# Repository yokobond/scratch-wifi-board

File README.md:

# scratch-wifi-board
Arduino and WiFi(ESP8266) speaking Scratch-Remote-Sensor-Protocol

## Overview

- [esp4scratch](esp4scratch) is a sketch for ESP8266/Arduino
- [esp4scratch_arduino](esp4scratch_arduino) is a sketch for Arduino Board which connect to ESP8266.
- [hardware/eagle](hardware/eagle) is a design data of Scratch WiFi Shield.

## Licence

[MIT](LICENCE)

## Author

[yokobond](https://github.com/yokobond)

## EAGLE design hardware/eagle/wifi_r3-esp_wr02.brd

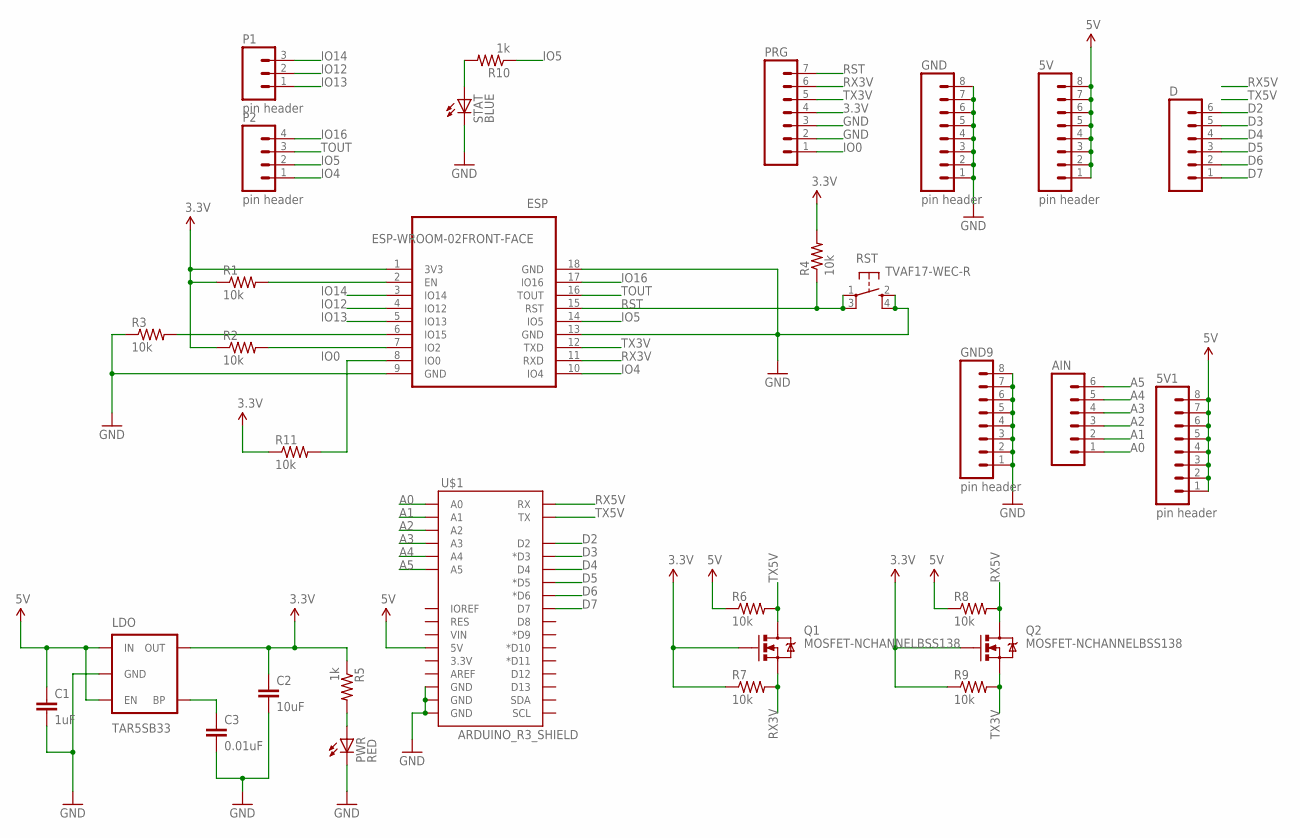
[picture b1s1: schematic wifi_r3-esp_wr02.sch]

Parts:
5V, 5V1: pin header; 1X08
AIN: M06SIP; 1X06
C1: 1uF; 0603-CAP
C2: 10uF; 0805
C3: 0.01uF; 0603-CAP
D: M06SIP; 1X06
ESP: ESP-WROOM-02FRONT-FACE; FRONT-FACE
GND, GND9: pin header; 1X08
LDO: TAR5SB33; SOT23-5
P1: pin header; 1X03
P2: pin header; 1X04
PRG: M07; 1X07
PWR: RED; LED-0603
Q1, Q2: MOSFET-NCHANNELBSS138; SOT23
R1, R2, R3, R4, R6, R7, R8, R9, R11: 10k; 0603-RES
R5, R10: 1k; 0603-RES
RST: TVAF17-WEC-R; KMR2
STAT: BLUE; LED-0603
U$1: ARDUINO_R3_SHIELD; UNO_R3_SHIELD

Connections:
3.3V: C2.1, ESP.1 (3V3), LDO.5 (OUT), PRG.4, Q1.1 (G), Q2.1 (G), R1.1, R2.1, R4.2, R5.1, R7.1, R9.1, R11.1
5V: 5V.1, 5V.2, 5V.3, 5V.4, 5V.5, 5V.6, 5V.7, 5V.8, 5V1.1, 5V1.2, 5V1.3, 5V1.4, 5V1.5, 5V1.6, 5V1.7, 5V1.8, C1.1, LDO.1 (IN), LDO.3 (EN), R6.1, R8.1, U$1.5V
A0: AIN.1, U$1.A0
A1: AIN.2, U$1.A1
A2: AIN.3, U$1.A2
A3: AIN.4, U$1.A3
A4: AIN.5, U$1.A4
A5: AIN.6, U$1.A5
D2: D.6, U$1.D2
D3: D.5, U$1.D3 (*D3)
D4: D.4, U$1.D4
D5: D.3, U$1.D5 (*D5)
D6: D.2, U$1.D6 (*D6)
D7: D.1, U$1.D7
GND: C1.2, C2.2, C3.2, ESP.9 (GND), ESP.13 (GND), ESP.18 (GND), GND.1, GND.2, GND.3, GND.4, GND.5, GND.6, GND.7, GND.8, GND9.1, GND9.2, GND9.3, GND9.4, GND9.5, GND9.6, GND9.7, GND9.8, LDO.2 (GND), PRG.2, PRG.3, PWR.C, R3.1, RST.2 (S), RST.4 (S), STAT.C, U$1.GND@0 (GND), U$1.GND@1 (GND), U$1.GND@2 (GND)
IO0: ESP.8 (IO0), PRG.1, R11.2
IO4: ESP.10 (IO4), P2.1
IO5: ESP.14 (IO5), P2.2, R10.1
IO12: ESP.4 (IO12), P1.2
IO13: ESP.5 (IO13), P1.1
IO14: ESP.3 (IO14), P1.3
IO16: ESP.17 (IO16), P2.4
unnamed: ESP.2 (EN), R1.2
unnamed: ESP.7 (IO2), R2.2
unnamed: ESP.6 (IO15), R3.2
unnamed: PWR.A, R5.2
unnamed: R10.2, STAT.A
unnamed: C3.1, LDO.4 (BP)
RST: ESP.15 (RST), PRG.7, R4.1, RST.1, RST.3
RX3V: ESP.11 (RXD), PRG.6, Q1.2 (S), R7.2
RX5V: Q2.3 (D), R8.2, U$1.RX
TOUT: ESP.16 (TOUT), P2.3
TX3V: ESP.12 (TXD), PRG.5, Q2.2 (S), R9.2
TX5V: Q1.3 (D), R6.2, U$1.TX

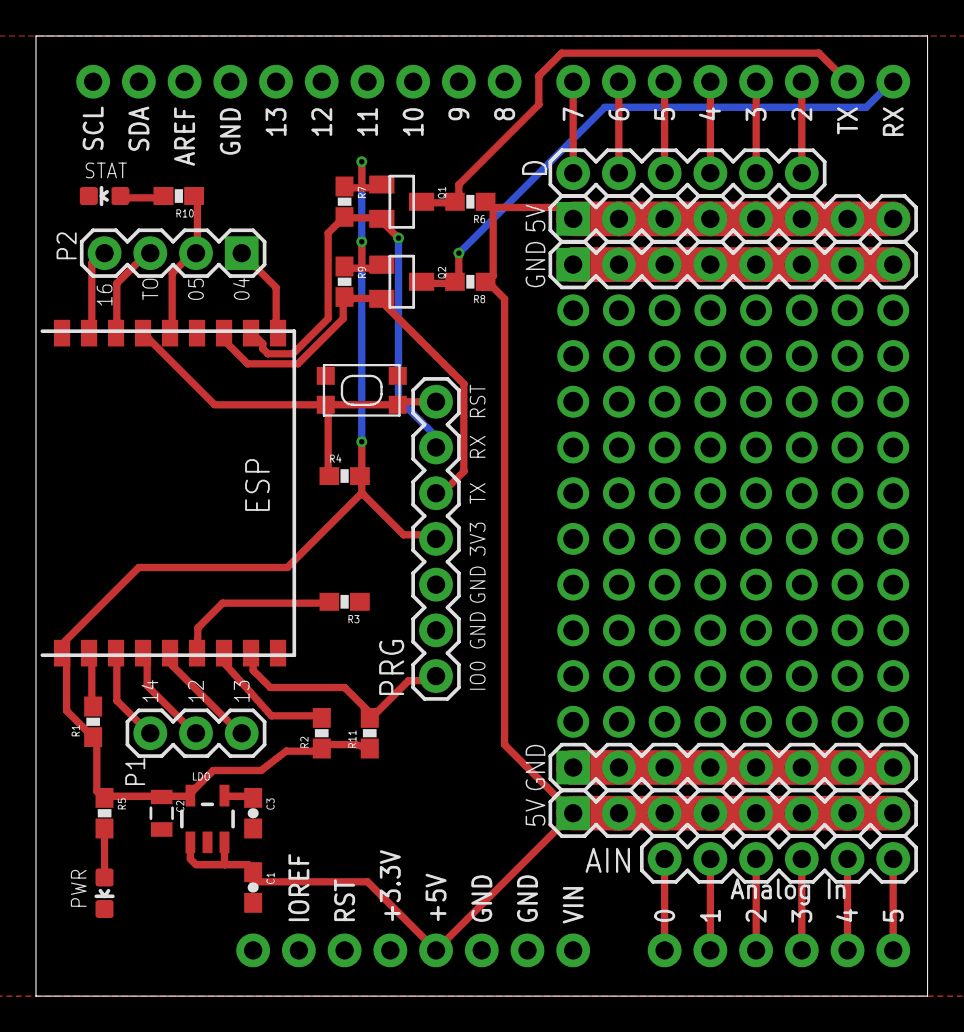
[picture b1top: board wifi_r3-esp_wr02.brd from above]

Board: 2 copper layers, 49.5 x 53.3 mm, 32 parts (1 on the bottom side), 34 nets.

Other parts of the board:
U$2: VIEWPOINT_M

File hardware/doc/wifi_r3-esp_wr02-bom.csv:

"Qty";"Value";"Device";"Package";"Parts";"Description";"PROD_ID";
"2";"";"M06SIP";"1X06";"AIN, D";"Header 6";"";
"1";"";"M07";"1X07";"PRG";"Header 7";"";
"1";"0.01uF";"CAP0603-CAP";"0603-CAP";"C3";"Capacitor";"";
"8";"10k";"RESISTOR0603";"0603-RES";"R1, R2, R3, R4, R6, R7, R8, R9";"Resistor";"";
"1";"10uF";"CAP0805";"0805";"C2";"Capacitor";"";
"3";"1k";"RESISTOR0603";"0603-RES";"R5, R10, R11";"Resistor";"";
"1";"1uF";"CAP0603-CAP";"0603-CAP";"C1";"Capacitor";"";
"1";"ARDUINO_R3_SHIELD";"ARDUINO_R3_SHIELD";"UNO_R3_SHIELD";"U$1";"Shield form compatible with the Arduino Uno R3.";"";
"1";"BLUE";"LED0603";"LED-0603";"STAT";"LEDs";"";
"1";"ESP-WROOM-02FRONT-FACE";"ESP-WROOM-02FRONT-FACE";"FRONT-FACE";"ESP";"WiFi module - ESP-WROOM-02";"";
"2";"MOSFET-NCHANNELBSS138";"MOSFET-NCHANNELBSS138";"SOT23";"Q1, Q2";"Common NMOSFET Parts";"TRANS-00830";
"1";"RED";"LED0603";"LED-0603";"PWR";"LEDs";"";
"1";"TAR5SB33";"TAR5SB33";"SOT23-5";"LDO";"TAR5SB LDO Regulator";"VREG-00822";
"1";"TVAF17-WEC-R";"SPST_TACT-KMR2";"KMR2";"RST";"SMT 6mm switch, EVQQ2 series";"";
"1";"pin header";"M03PTH";"1X03";"P1";"Header 3";"";
"1";"pin header";"M04PTH";"1X04";"P2";"Header 4";"";
"4";"pin header";"M081X08";"1X08";"5V, 5V1, GND, GND9";"Header 8";"";

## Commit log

2016-07-10 Initial commit
    Implemented Scratch Remote Sensor Protocol and broadcast IP address.
2016-07-10 Changed indent to 4 spaces
2016-07-11 Remove and ignore IDE specific files.
2016-07-20 Changed to save multicast state in json on SPIFF.
2016-07-20 Changed to save scratch_clients IPs in json on SPIFF.
2016-07-23 Fixed to reference error of SPIFFS.
2016-08-02 Add include guard.
2016-08-03 Add hardware files
2016-08-04 Add readme
2016-08-04 Add Licence
2016-08-05 Fix to send Scratch to Arduino message and control 'd13', 'pwm3'.
2016-08-05 Reduce processing by skip stacked commands.
2016-08-05 Fix to remove registered Scratch from other machine.
2016-08-13 Add poster and flyer for Scratch@MIT2016

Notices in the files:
parts and their libraries:
SparkFun-Connectors: Licensing: Creative Commons ShareAlike 4.0 International - https://creativecommons.org/licenses/by-sa/4.0
